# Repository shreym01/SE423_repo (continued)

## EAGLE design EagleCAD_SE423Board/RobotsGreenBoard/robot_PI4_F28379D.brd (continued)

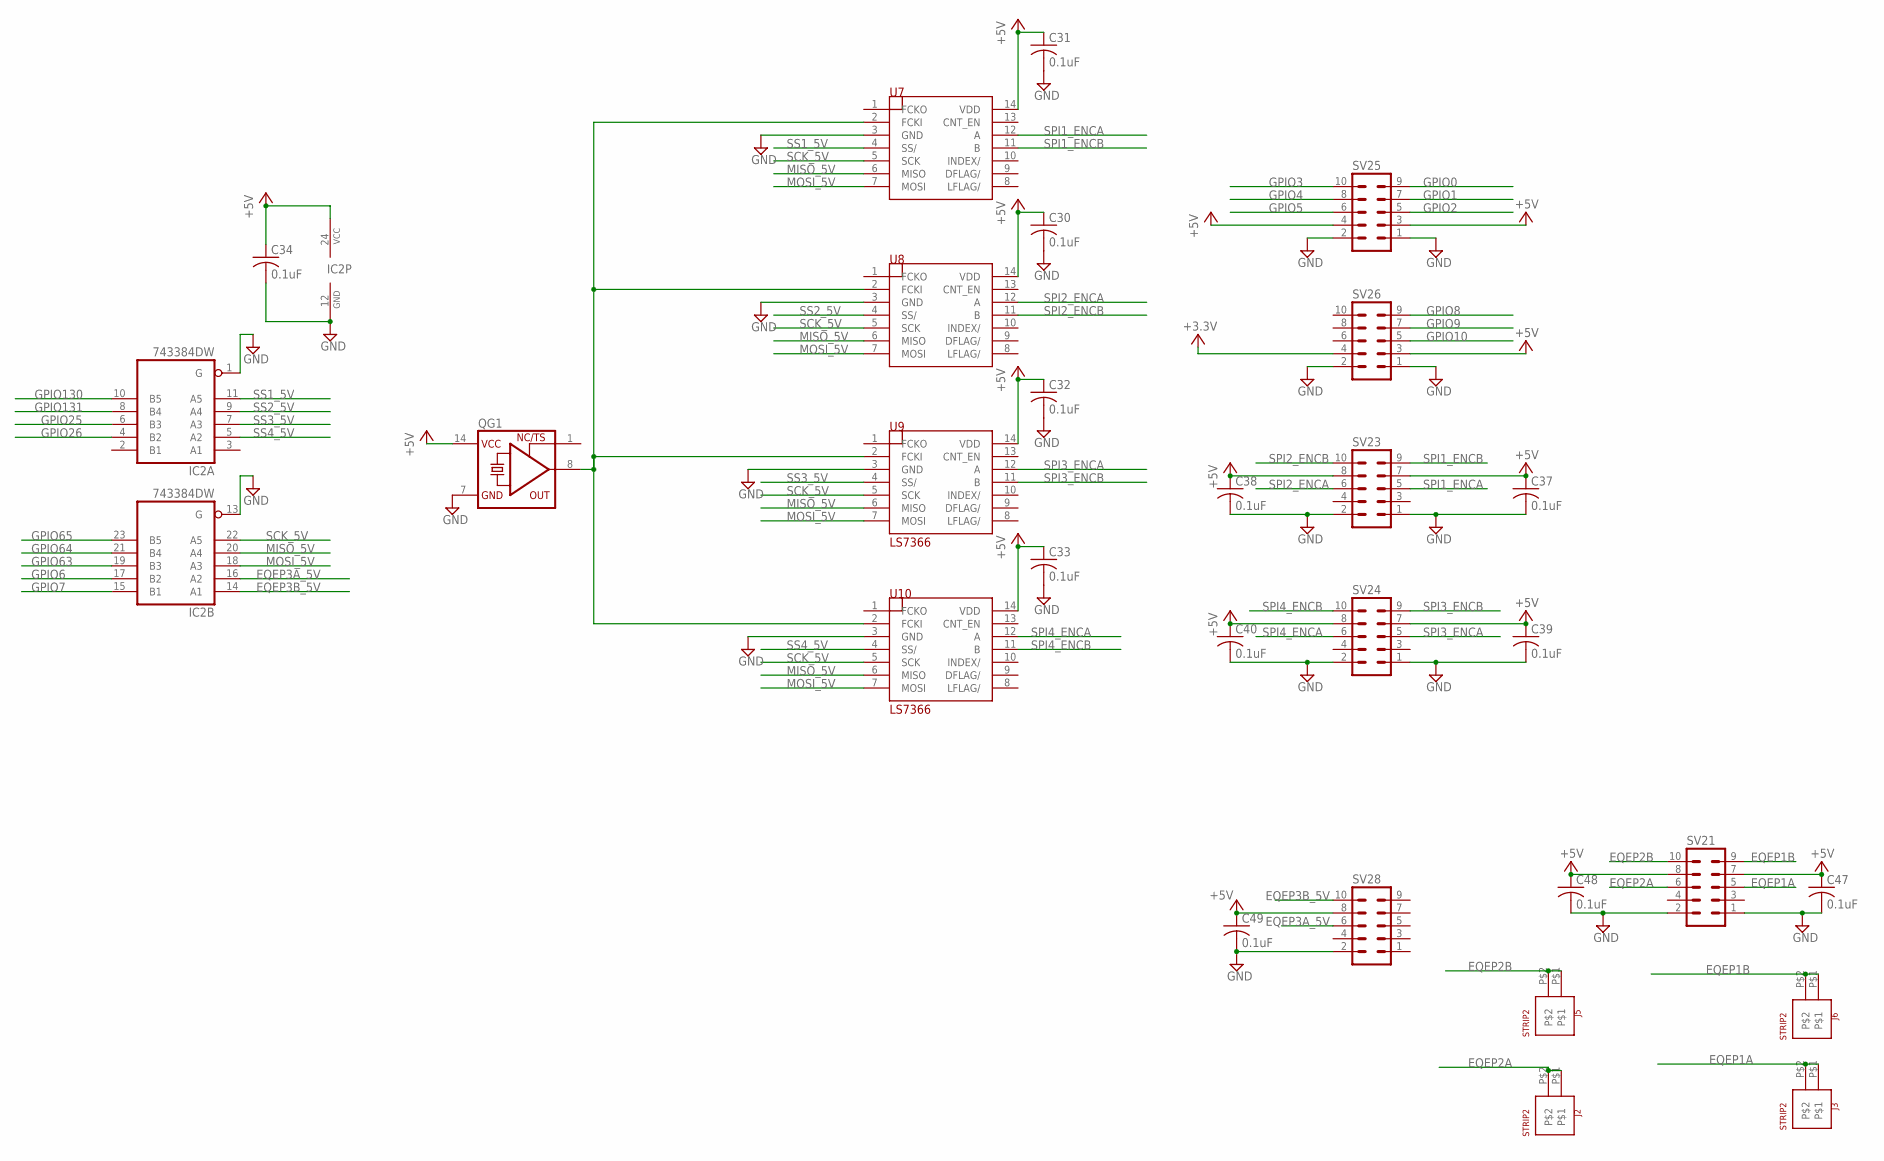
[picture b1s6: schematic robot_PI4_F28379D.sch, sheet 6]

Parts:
C30, C31, C32, C33, C34, C37, C38, C39, C40, C47, C48, C49: 0.1uF; C1206
IC2: 743384DW; SO24W
J2, J3, J5, J6: STRIP2
QG1: XO-14; DIL14S
SV21, SV23, SV24, SV25, SV26, SV28: MA05-2
U7, U8: LS7366R; SO14
U9, U10: LS7366; SO14

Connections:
+3.3V: SV26.4; also elsewhere on the board
+5V: C30.1, C31.1, C32.1, C33.1, C34.1, C37.1, C38.1, C39.1, C40.1, C47.1, C48.1, C49.1, IC2.24 (VCC), QG1.14 (VCC), SV21.7, SV21.8, SV23.7, SV23.8, SV24.7, SV24.8, SV25.3, SV25.4, SV26.3, SV28.8, U7.14 (VDD), U8.14 (VDD), U9.14 (VDD), U10.14 (VDD); also elsewhere on the board
EQEP1A: J3.P$1, J3.P$2, SV21.5
EQEP1B: J6.P$1, J6.P$2, SV21.9
EQEP2A: J2.P$1, J2.P$2, SV21.6
EQEP2B: J5.P$1, J5.P$2, SV21.10
EQEP3A_5V: IC2.16 (A2), SV28.6
EQEP3B_5V: IC2.14 (A1), SV28.10
GND: C30.2, C31.2, C32.2, C33.2, C34.2, C37.2, C38.2, C39.2, C40.2, C47.2, C48.2, C49.2, IC2.1 (G), IC2.12 (GND), IC2.13 (G), QG1.7 (GND), SV21.1, SV21.2, SV23.1, SV23.2, SV24.1, SV24.2, SV25.1, SV25.2, SV26.1, SV26.2, SV28.2, U7.3 (GND), U8.3 (GND), U9.3 (GND), U10.3 (GND); also elsewhere on the board
GPIO0: SV25.9; also elsewhere on the board
GPIO1: SV25.7; also elsewhere on the board
GPIO2: SV25.5; also elsewhere on the board
GPIO3: SV25.10; also elsewhere on the board
GPIO4: SV25.8; also elsewhere on the board
GPIO5: SV25.6; also elsewhere on the board
GPIO6: IC2.17 (B2); also elsewhere on the board
GPIO7: IC2.15 (B1); also elsewhere on the board
GPIO8: SV26.9; also elsewhere on the board
GPIO9: SV26.7; also elsewhere on the board
GPIO10: SV26.5; also elsewhere on the board
GPIO25: IC2.6 (B3); also elsewhere on the board
GPIO26: IC2.4 (B2); also elsewhere on the board
GPIO63: IC2.19 (B3); also elsewhere on the board
GPIO64: IC2.21 (B4); also elsewhere on the board
GPIO65: IC2.23 (B5); also elsewhere on the board
GPIO130: IC2.10 (B5); also elsewhere on the board
GPIO131: IC2.8 (B4); also elsewhere on the board
MISO_5V: IC2.20 (A4), U7.6 (MISO), U8.6 (MISO), U9.6 (MISO), U10.6 (MISO)
MOSI_5V: IC2.18 (A3), U7.7 (MOSI), U8.7 (MOSI), U9.7 (MOSI), U10.7 (MOSI)
unnamed: QG1.8 (OUT), U7.2 (FCKI), U8.2 (FCKI), U9.2 (FCKI), U10.2 (FCKI)
SCK_5V: IC2.22 (A5), U7.5 (SCK), U8.5 (SCK), U9.5 (SCK), U10.5 (SCK)
SPI1_ENCA: SV23.5, U7.12 (A)
SPI1_ENCB: SV23.9, U7.11 (B)
SPI2_ENCA: SV23.6, U8.12 (A)
SPI2_ENCB: SV23.10, U8.11 (B)
SPI3_ENCA: SV24.5, U9.12 (A)
SPI3_ENCB: SV24.9, U9.11 (B)
SPI4_ENCA: SV24.6, U10.12 (A)
SPI4_ENCB: SV24.10, U10.11 (B)
SS1_5V: IC2.11 (A5), U7.4 (SS/)
SS2_5V: IC2.9 (A4), U8.4 (SS/)
SS3_5V: IC2.7 (A3), U9.4 (SS/)
SS4_5V: IC2.5 (A2), U10.4 (SS/)

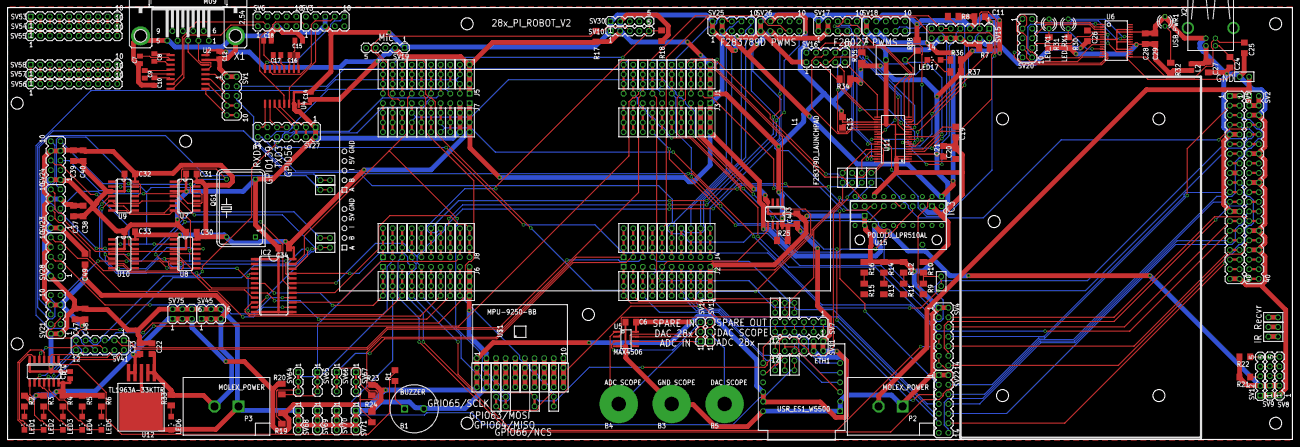
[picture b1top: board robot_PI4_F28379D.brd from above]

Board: 2 copper layers, 339.1 x 114.0 mm, 270 parts (0 on the bottom side), 281 nets.

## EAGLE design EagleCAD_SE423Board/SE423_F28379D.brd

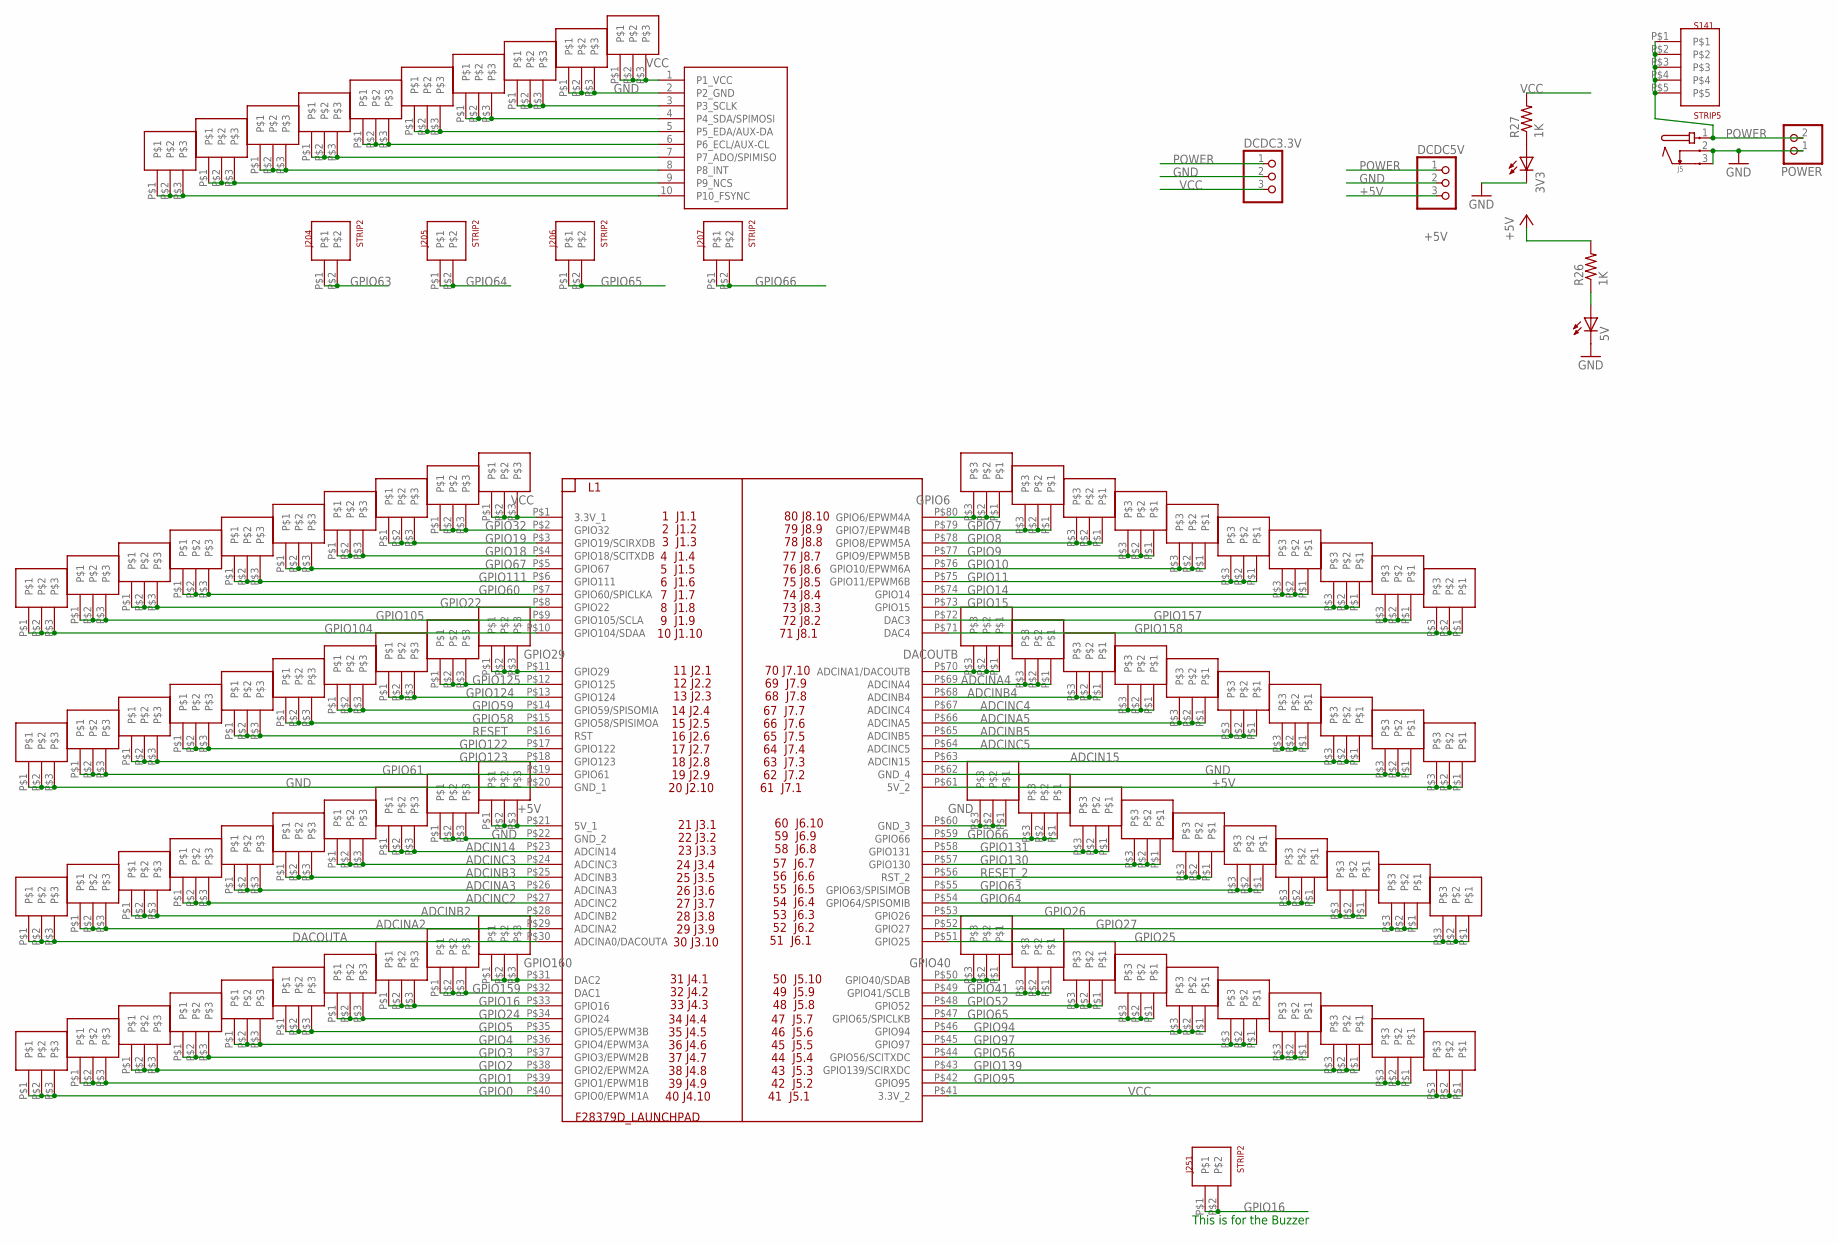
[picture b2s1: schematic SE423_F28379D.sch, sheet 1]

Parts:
3V3, 5V: LEDCHIPLED_1206; CHIPLED_1206
DCDC3.3V, DCDC5V: PINHD-1X3; 1X03
J5: JACK-PMS
J10, J14, J15, J16, J17, J18, J19, J20, J21, J28, J29, J30, J31, J32, J33, J98, J99, J100, J101, J102, J103, J104, J105, J106, J107, J108, J109, J110, J111, J112, J113, J114, J115, J116, J117, J118, J119, J120, J121, J122, J123, J124, J125, J126, J127, J128, J129, J130, J131, J132, J133, J134, J135, J136, J137, J138, J139, J140, J141, J142, J143, J144, J145, J146, J147, J148, J149, J150, J151, J152, J153, J154, J155, J156, J157, J158, J159, J160, J161, J162, J163, J164, J165, J166, J167, J168, J169, J170, J176, J177: STRIP3
J204, J205, J206, J207, J251: STRIP2
L1: F28379D_LAUNCHPAD
POWER: PINHD-1X2; 1X02
R26, R27: 1K; M1206
S141: STRIP5
U$1: MPU-9250-BB

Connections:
+5V: DCDC5V.3, J103.P$1, J103.P$2, J103.P$3, J152.P$1, J152.P$2, J152.P$3, L1.P$21 (5V_1), L1.P$61 (5V_2), R26.2; also elsewhere on the board
ADCIN14: J105.P$1, J105.P$2, J105.P$3, L1.P$23 (ADCIN14)
ADCIN15: J150.P$1, J150.P$2, J150.P$3, L1.P$63 (ADCIN15)
ADCINA2: J111.P$1, J111.P$2, J111.P$3, L1.P$29 (ADCINA2); also elsewhere on the board
ADCINA3: J108.P$1, J108.P$2, J108.P$3, L1.P$26 (ADCINA3); also elsewhere on the board
ADCINA4: J144.P$1, J144.P$2, J144.P$3, L1.P$69 (ADCINA4)
ADCINA5: J147.P$1, J147.P$2, J147.P$3, L1.P$66 (ADCINA5)
ADCINB2: J110.P$1, J110.P$2, J110.P$3, L1.P$28 (ADCINB2)
ADCINB3: J107.P$1, J107.P$2, J107.P$3, L1.P$25 (ADCINB3)
ADCINB4: J145.P$1, J145.P$2, J145.P$3, L1.P$68 (ADCINB4); also elsewhere on the board
ADCINB5: J148.P$1, J148.P$2, J148.P$3, L1.P$65 (ADCINB5)
ADCINC2: J109.P$1, J109.P$2, J109.P$3, L1.P$27 (ADCINC2)
ADCINC3: J106.P$1, J106.P$2, J106.P$3, L1.P$24 (ADCINC3)
ADCINC4: J146.P$1, J146.P$2, J146.P$3, L1.P$67 (ADCINC4)
ADCINC5: J149.P$1, J149.P$2, J149.P$3, L1.P$64 (ADCINC5)
DACOUTA: J112.P$1, J112.P$2, J112.P$3, L1.P$30 (ADCINA0/DACOUTA)
DACOUTB: J143.P$1, J143.P$2, J143.P$3, L1.P$70 (ADCINA1/DACOUTB)
GND: 3V3.C, 5V.C, DCDC3.3V.2, DCDC5V.2, J5.2, J5.3, J102.P$1, J102.P$2, J102.P$3, J104.P$1, J104.P$2, J104.P$3, J124.P$1, J124.P$2, J124.P$3, J151.P$1, J151.P$2, J151.P$3, J153.P$1, J153.P$2, J153.P$3, L1.P$20 (GND_1), L1.P$22 (GND_2), L1.P$60 (GND_3), L1.P$62 (GND_4), POWER.1, U$1.2 (P2_GND); also elsewhere on the board
GPIO0: J122.P$1, J122.P$2, J122.P$3, L1.P$40 (GPIO0/EPWM1A); also elsewhere on the board
GPIO1: J121.P$1, J121.P$2, J121.P$3, L1.P$39 (GPIO1/EPWM1B); also elsewhere on the board
GPIO2: J120.P$1, J120.P$2, J120.P$3, L1.P$38 (GPIO2/EPWM2A); also elsewhere on the board
GPIO3: J119.P$1, J119.P$2, J119.P$3, L1.P$37 (GPIO3/EPWM2B); also elsewhere on the board
GPIO4: J118.P$1, J118.P$2, J118.P$3, L1.P$36 (GPIO4/EPWM3A); also elsewhere on the board
GPIO5: J117.P$1, J117.P$2, J117.P$3, L1.P$35 (GPIO5/EPWM3B); also elsewhere on the board
GPIO6: J133.P$1, J133.P$2, J133.P$3, L1.P$80 (GPIO6/EPWM4A); also elsewhere on the board
GPIO7: J134.P$1, J134.P$2, J134.P$3, L1.P$79 (GPIO7/EPWM4B); also elsewhere on the board
GPIO8: J135.P$1, J135.P$2, J135.P$3, L1.P$78 (GPIO8/EPWM5A); also elsewhere on the board
GPIO9: J136.P$1, J136.P$2, J136.P$3, L1.P$77 (GPIO9/EPWM5B); also elsewhere on the board
GPIO10: J137.P$1, J137.P$2, J137.P$3, L1.P$76 (GPIO10/EPWM6A); also elsewhere on the board
GPIO11: J138.P$1, J138.P$2, J138.P$3, L1.P$75 (GPIO11/EPWM6B); also elsewhere on the board
GPIO14: J139.P$1, J139.P$2, J139.P$3, L1.P$74 (GPIO14); also elsewhere on the board
GPIO15: J140.P$1, J140.P$2, J140.P$3, L1.P$73 (GPIO15); also elsewhere on the board
GPIO16: J115.P$1, J115.P$2, J115.P$3, J251.P$1, J251.P$2, L1.P$33 (GPIO16)
GPIO18: J16.P$1, J16.P$2, J16.P$3, L1.P$4 (GPIO18/SCITXDB); also elsewhere on the board
GPIO19: J15.P$1, J15.P$2, J15.P$3, L1.P$3 (GPIO19/SCIRXDB); also elsewhere on the board
GPIO22: J20.P$1, J20.P$2, J20.P$3, L1.P$8 (GPIO22); also elsewhere on the board
GPIO24: J116.P$1, J116.P$2, J116.P$3, L1.P$34 (GPIO24); also elsewhere on the board
GPIO25: J162.P$1, J162.P$2, J162.P$3, L1.P$51 (GPIO25); also elsewhere on the board
GPIO26: J160.P$1, J160.P$2, J160.P$3, L1.P$53 (GPIO26); also elsewhere on the board
GPIO27: J161.P$1, J161.P$2, J161.P$3, L1.P$52 (GPIO27); also elsewhere on the board
GPIO29: J29.P$1, J29.P$2, J29.P$3, L1.P$11 (GPIO29); also elsewhere on the board
GPIO32: J14.P$1, J14.P$2, J14.P$3, L1.P$2 (GPIO32); also elsewhere on the board
GPIO40: J163.P$1, J163.P$2, J163.P$3, L1.P$50 (GPIO40/SDAB); also elsewhere on the board
GPIO41: J164.P$1, J164.P$2, J164.P$3, L1.P$49 (GPIO41/SCLB); also elsewhere on the board
GPIO52: J165.P$1, J165.P$2, J165.P$3, L1.P$48 (GPIO52)
GPIO56: J169.P$1, J169.P$2, J169.P$3, L1.P$44 (GPIO56/SCITXDC); also elsewhere on the board
GPIO58: J33.P$1, J33.P$2, J33.P$3, L1.P$15 (GPIO58/SPISIMOA); also elsewhere on the board
GPIO59: J32.P$1, J32.P$2, J32.P$3, L1.P$14 (GPIO59/SPISOMIA); also elsewhere on the board
GPIO60: J19.P$1, J19.P$2, J19.P$3, L1.P$7 (GPIO60/SPICLKA); also elsewhere on the board
GPIO61: J101.P$1, J101.P$2, J101.P$3, L1.P$19 (GPIO61); also elsewhere on the board
GPIO63: J158.P$1, J158.P$2, J158.P$3, J204.P$1, J204.P$2, L1.P$55 (GPIO63/SPISIMOB); also elsewhere on the board
GPIO64: J159.P$1, J159.P$2, J159.P$3, J205.P$1, J205.P$2, L1.P$54 (GPIO64/SPISOMIB); also elsewhere on the board
GPIO65: J166.P$1, J166.P$2, J166.P$3, J206.P$1, J206.P$2, L1.P$47 (GPIO65/SPICLKB); also elsewhere on the board
GPIO66: J154.P$1, J154.P$2, J154.P$3, J207.P$1, J207.P$2, L1.P$59 (GPIO66)
GPIO67: J17.P$1, J17.P$2, J17.P$3, L1.P$5 (GPIO67)
GPIO94: J167.P$1, J167.P$2, J167.P$3, L1.P$46 (GPIO94); also elsewhere on the board
GPIO95: J176.P$1, J176.P$2, J176.P$3, L1.P$42 (GPIO95); also elsewhere on the board
GPIO97: J168.P$1, J168.P$2, J168.P$3, L1.P$45 (GPIO97); also elsewhere on the board
GPIO104: J28.P$1, J28.P$2, J28.P$3, L1.P$10 (GPIO104/SDAA)
GPIO105: J21.P$1, J21.P$2, J21.P$3, L1.P$9 (GPIO105/SCLA)
GPIO111: J18.P$1, J18.P$2, J18.P$3, L1.P$6 (GPIO111); also elsewhere on the board
GPIO122: J99.P$1, J99.P$2, J99.P$3, L1.P$17 (GPIO122); also elsewhere on the board
GPIO123: J100.P$1, J100.P$2, J100.P$3, L1.P$18 (GPIO123); also elsewhere on the board
GPIO124: J31.P$1, J31.P$2, J31.P$3, L1.P$13 (GPIO124); also elsewhere on the board
GPIO125: J30.P$1, J30.P$2, J30.P$3, L1.P$12 (GPIO125); also elsewhere on the board
GPIO130: J156.P$1, J156.P$2, J156.P$3, L1.P$57 (GPIO130); also elsewhere on the board
GPIO131: J155.P$1, J155.P$2, J155.P$3, L1.P$58 (GPIO131); also elsewhere on the board
GPIO139: J170.P$1, J170.P$2, J170.P$3, L1.P$43 (GPIO139/SCIRXDC); also elsewhere on the board
GPIO157: J141.P$1, J141.P$2, J141.P$3, L1.P$72 (DAC3); also elsewhere on the board
GPIO158: J142.P$1, J142.P$2, J142.P$3, L1.P$71 (DAC4); also elsewhere on the board
GPIO159: J114.P$1, J114.P$2, J114.P$3, L1.P$32 (DAC1); also elsewhere on the board
GPIO160: J113.P$1, J113.P$2, J113.P$3, L1.P$31 (DAC2); also elsewhere on the board
unnamed: 3V3.A, R27.1
unnamed: 5V.A, R26.1
unnamed: J125.P$1, J125.P$2, J125.P$3, U$1.3 (P3_SCLK)
unnamed: J126.P$1, J126.P$2, J126.P$3, U$1.4 (P4_SDA/SPIMOSI)
unnamed: J127.P$1, J127.P$2, J127.P$3, U$1.5 (P5_EDA/AUX-DA)
unnamed: J128.P$1, J128.P$2, J128.P$3, U$1.6 (P6_ECL/AUX-CL)
unnamed: J129.P$1, J129.P$2, J129.P$3, U$1.7 (P7_ADO/SPIMISO)
unnamed: J130.P$1, J130.P$2, J130.P$3, U$1.8 (P8_INT)
unnamed: J131.P$1, J131.P$2, J131.P$3, U$1.9 (P9_NCS)
unnamed: J132.P$1, J132.P$2, J132.P$3, U$1.10 (P10_FSYNC)
POWER: DCDC3.3V.1, DCDC5V.1, J5.1, POWER.2, S141.P$1, S141.P$2, S141.P$3, S141.P$4, S141.P$5; also elsewhere on the board
RESET: J98.P$1, J98.P$2, J98.P$3, L1.P$16 (RST)
RESET_2: J157.P$1, J157.P$2, J157.P$3, L1.P$56 (RST_2)
VCC: DCDC3.3V.3, J10.P$1, J10.P$2, J10.P$3, J123.P$1, J123.P$2, J123.P$3, J177.P$1, J177.P$2, J177.P$3, L1.P$1 (3.3V_1), L1.P$41 (3.3V_2), R27.2, U$1.1 (P1_VCC); also elsewhere on the board

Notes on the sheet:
This is for the Buzzer

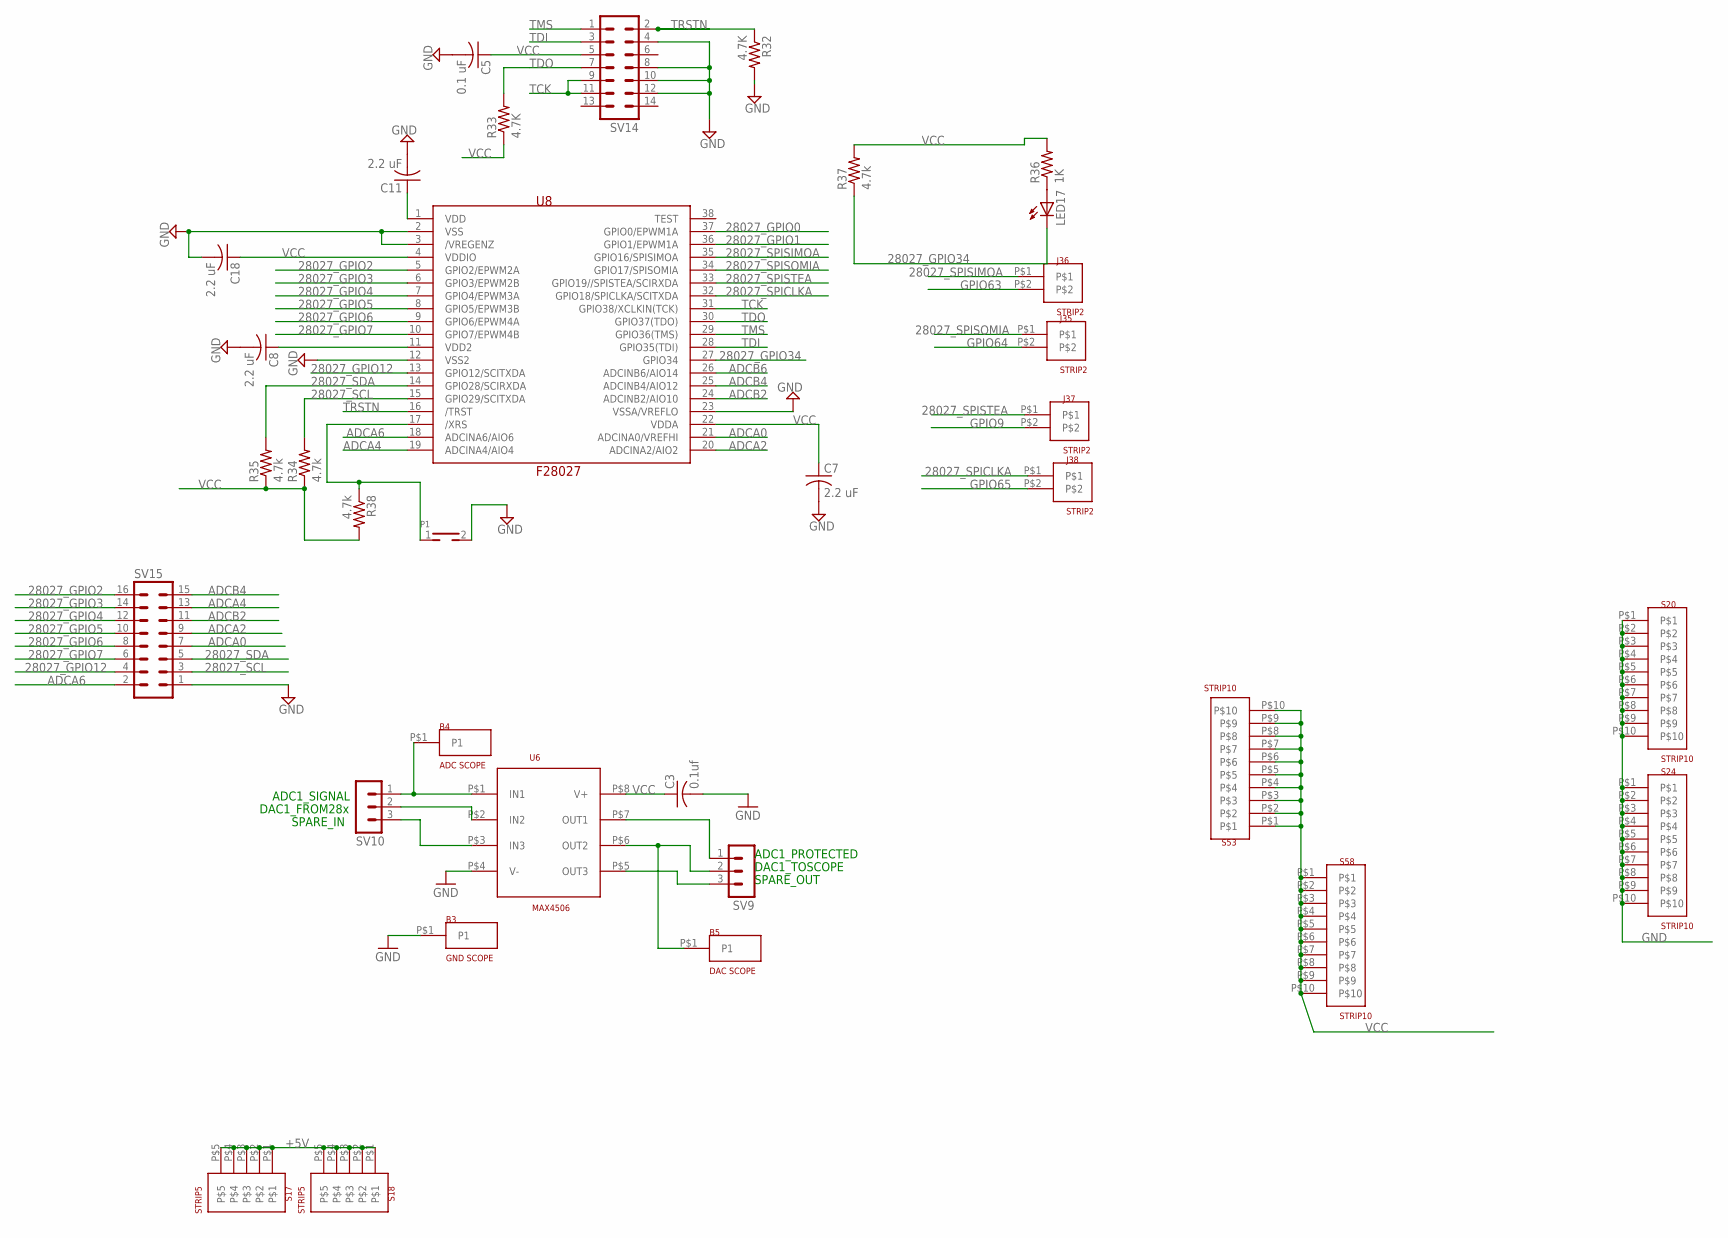
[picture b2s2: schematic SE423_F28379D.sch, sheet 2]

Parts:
B3: GND SCOPE; BANANA_MALE
B4: ADC SCOPE; BANANA_MALE
B5: DAC SCOPE; BANANA_MALE
C3: 0.1uf; C1206
C5: 0.1 uF; C1206
C7, C8, C11, C18: 2.2 uF; C1206
J35, J36, J37, J38: STRIP2
LED17: LEDCHIPLED_1206; CHIPLED_1206
P1: TH_PUSHBOTTON; TH_PUSHBUTTON
R32, R33: 4.7K; M1206
R34, R35, R37, R38: 4.7k; M1206
R36: 1K; M1206
S17, S18: STRIP5
S20, S24, S53, S58: STRIP10
SV9, SV10: MA03-1
SV14: MA07-2
SV15: MA08-2
U6: MAX4506; SOIC-8
U8: F28027; DA38

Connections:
28027_GPIO0: U8.37 (GPIO0/EPWM1A); also elsewhere on the board
28027_GPIO1: U8.36 (GPIO1/EPWM1A); also elsewhere on the board
28027_GPIO2: SV15.16, U8.5 (GPIO2/EPWM2A)
28027_GPIO3: SV15.14, U8.6 (GPIO3/EPWM2B)
28027_GPIO4: SV15.12, U8.7 (GPIO4/EPWM3A)
28027_GPIO5: SV15.10, U8.8 (GPIO5/EPWM3B)
28027_GPIO6: SV15.8, U8.9 (GPIO6/EPWM4A)
28027_GPIO7: SV15.6, U8.10 (GPIO7/EPWM4B)
28027_GPIO12: SV15.4, U8.13 (GPIO12/SCITXDA)
28027_GPIO34: LED17.C, R37.1, U8.27 (GPIO34)
28027_SCL: R34.2, SV15.3, U8.15 (GPIO29/SCITXDA)
28027_SDA: R35.2, SV15.5, U8.14 (GPIO28/SCIRXDA)
28027_SPICLKA: J38.P$1, U8.32 (GPIO18/SPICLKA/SCITXDA)
28027_SPISIMOA: J36.P$1, U8.35 (GPIO16/SPISIMOA)
28027_SPISOMIA: J35.P$1, U8.34 (GPIO17/SPISOMIA)
28027_SPISTEA: J37.P$1, U8.33 (GPIO19//SPISTEA/SCIRXDA)
+5V: S17.P$1, S17.P$2, S17.P$3, S17.P$4, S17.P$5, S18.P$1, S18.P$2, S18.P$3, S18.P$4, S18.P$5; also elsewhere on the board
ADCA0: SV15.7, U8.21 (ADCINA0/VREFHI)
ADCA2: SV15.9, U8.20 (ADCINA2/AIO2)
ADCA4: SV15.13, U8.19 (ADCINA4/AIO4)
ADCA6: SV15.2, U8.18 (ADCINA6/AIO6)
ADCB2: SV15.11, U8.24 (ADCINB2/AIO10)
ADCB4: SV15.15, U8.25 (ADCINB4/AIO12)
ADCB6: U8.26 (ADCINB6/AIO14)
GND: B3.P$1, C3.2, C5.2, C7.2, C8.2, C11.2, C18.2, P1.2, R32.2, S20.P$1, S20.P$2, S20.P$3, S20.P$4, S20.P$5, S20.P$6, S20.P$7, S20.P$8, S20.P$9, S20.P$10, S24.P$1, S24.P$2, S24.P$3, S24.P$4, S24.P$5, S24.P$6, S24.P$7, S24.P$8, S24.P$9, S24.P$10, SV14.4, SV14.8, SV14.10, SV14.12, SV15.1, U6.P$4 (V-), U8.2 (VSS), U8.3 (/VREGENZ), U8.12 (VSS2), U8.23 (VSSA/VREFLO); also elsewhere on the board
GPIO9: J37.P$2; also elsewhere on the board
GPIO63: J36.P$2; also elsewhere on the board
GPIO64: J35.P$2; also elsewhere on the board
GPIO65: J38.P$2; also elsewhere on the board
unnamed: SV9.1, U6.P$7 (OUT1)
unnamed: B5.P$1, SV9.2, U6.P$6 (OUT2)
unnamed: SV9.3, U6.P$5 (OUT3)
unnamed: B4.P$1, SV10.1, U6.P$1 (IN1)
unnamed: SV10.2, U6.P$2 (IN2)
unnamed: SV10.3, U6.P$3 (IN3)
unnamed: C11.1, U8.1 (VDD)
unnamed: C8.1, U8.11 (VDD2)
unnamed: P1.1, R38.1, U8.17 (/XRS)
unnamed: LED17.A, R36.1
TCK: SV14.9, SV14.11, U8.31 (GPIO38/XCLKIN(TCK))
TDI: SV14.3, U8.28 (GPIO35(TDI))
TDO: R33.2, SV14.7, U8.30 (GPIO37(TDO))
TMS: SV14.1, U8.29 (GPIO36(TMS))
TRSTN: R32.1, SV14.2, U8.16 (/TRST)
VCC: C3.1, C5.1, C7.1, C18.1, R33.1, R34.1, R35.1, R36.2, R37.2, R38.2, S53.P$1, S53.P$2, S53.P$3, S53.P$4, S53.P$5, S53.P$6, S53.P$7, S53.P$8, S53.P$9, S53.P$10, S58.P$1, S58.P$2, S58.P$3, S58.P$4, S58.P$5, S58.P$6, S58.P$7, S58.P$8, S58.P$9, S58.P$10, SV14.5, U6.P$8 (V+), U8.4 (VDDIO), U8.22 (VDDA); also elsewhere on the board

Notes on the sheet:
ADC1_SIGNAL
ADC1_PROTECTED
DAC1_FROM28x
DAC1_TOSCOPE
SPARE_IN
SPARE_OUT

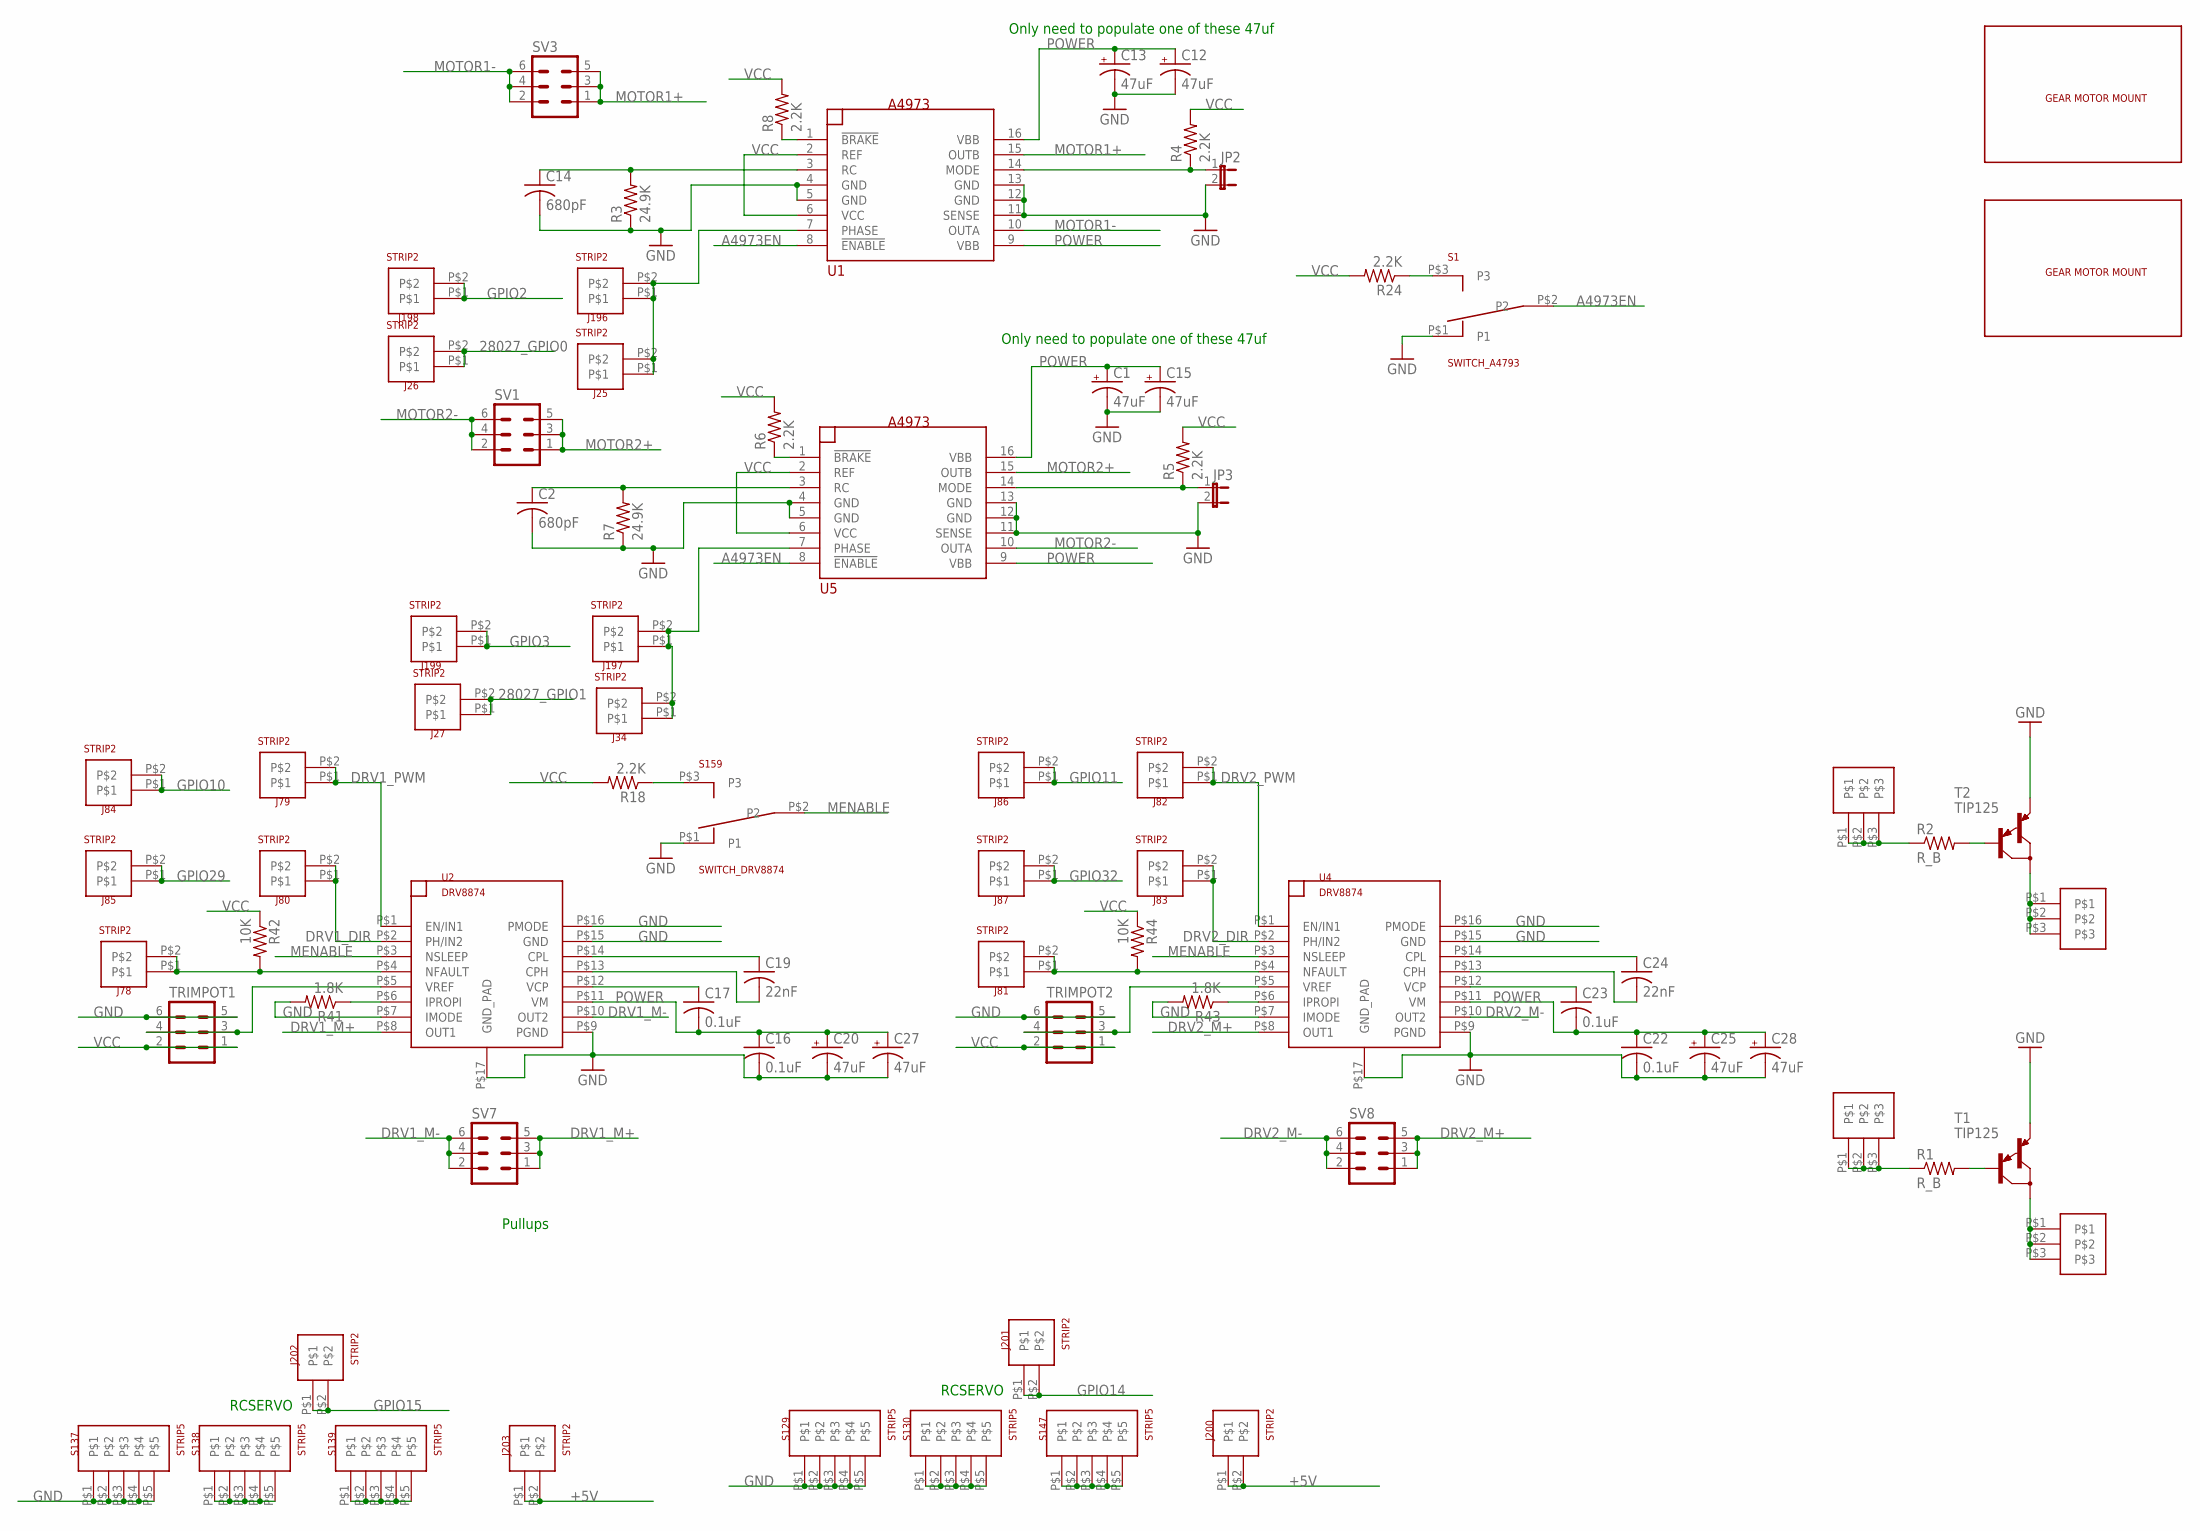
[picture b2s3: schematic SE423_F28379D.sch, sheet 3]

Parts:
C1, C12, C13, C15, C20, C25, C27, C28: 47uF; 153CLV-0810
C2, C14: 680pF; C1206
C16, C17, C22, C23: 0.1uF; C1206
C19, C24: 22nF; C1206
J4, J6, J23, J24: STRIP3
J25, J26, J27, J34, J78, J79, J80, J81, J82, J83, J84, J85, J86, J87, J196, J197, J198, J199, J200, J201, J202, J203: STRIP2
JP2, JP3: JP1E; JP1
R1, R2: R_B; 0207/10
R3, R7: 24.9K; M1206
R4, R5, R6, R8, R18, R24: 2.2K; M1206
R41, R43: 1.8K; M1206
R42, R44: 10K; M1206
S1: SWITCH_A4793; SWITCH_SLIDE
S129, S130, S137, S138, S139, S147: STRIP5
S159: SWITCH_DRV8874; SWITCH_SLIDE
SV1, SV3, SV7, SV8: MA03-2
T1, T2: TIP125; TO220
TRIMPOT1, TRIMPOT2: MA03-2
U1, U5: A4973; SO16W_LONGERPINS
U2, U4: DRV8874; HTSSOP16
U$2, U$3: GEARMOTOR_MOUNT

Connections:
28027_GPIO0: J26.P$1, J26.P$2; also elsewhere on the board
28027_GPIO1: J27.P$1, J27.P$2; also elsewhere on the board
+5V: J200.P$1, J200.P$2, J203.P$1, J203.P$2; also elsewhere on the board
A4973EN: S1.P$2 (P2), U1.8 (!ENABLE), U5.8 (!ENABLE)
DRV1_DIR: J80.P$1, J80.P$2, U2.P$2 (PH/IN2)
DRV1_M+: SV7.1, SV7.3, SV7.5, U2.P$8 (OUT1)
DRV1_M-: SV7.2, SV7.4, SV7.6, U2.P$10 (OUT2)
DRV1_PWM: J79.P$1, J79.P$2, U2.P$1 (EN/IN1)
DRV2_DIR: J83.P$1, J83.P$2, U4.P$2 (PH/IN2)
DRV2_M+: SV8.1, SV8.3, SV8.5, U4.P$8 (OUT1)
DRV2_M-: SV8.2, SV8.4, SV8.6, U4.P$10 (OUT2)
DRV2_PWM: J82.P$1, J82.P$2, U4.P$1 (EN/IN1)
GND: C1.-, C2.2, C12.-, C13.-, C14.2, C15.-, C16.2, C20.-, C22.2, C25.-, C27.-, C28.-, JP2.2, JP3.2, R3.1, R7.1, R41.2, R43.2, S1.P$1 (P1), S129.P$1, S129.P$2, S129.P$3, S129.P$4, S129.P$5, S137.P$1, S137.P$2, S137.P$3, S137.P$4, S137.P$5, S159.P$1 (P1), T1.3 (E), T2.3 (E), TRIMPOT1.5, TRIMPOT1.6, TRIMPOT2.5, TRIMPOT2.6, U1.4 (GND), U1.5 (GND), U1.11 (SENSE), U1.12 (GND), U1.13 (GND), U2.P$7 (IMODE), U2.P$9 (PGND), U2.P$15 (GND), U2.P$16 (PMODE), U2.P$17 (GND_PAD), U4.P$7 (IMODE), U4.P$9 (PGND), U4.P$15 (GND), U4.P$16 (PMODE), U4.P$17 (GND_PAD), U5.4 (GND), U5.5 (GND), U5.11 (SENSE), U5.12 (GND), U5.13 (GND); also elsewhere on the board
GPIO2: J198.P$1, J198.P$2; also elsewhere on the board
GPIO3: J199.P$1, J199.P$2; also elsewhere on the board
GPIO10: J84.P$1, J84.P$2; also elsewhere on the board
GPIO11: J86.P$1, J86.P$2; also elsewhere on the board
GPIO14: J201.P$1, J201.P$2; also elsewhere on the board
GPIO15: J202.P$1, J202.P$2; also elsewhere on the board
GPIO29: J85.P$1, J85.P$2; also elsewhere on the board
GPIO32: J87.P$1, J87.P$2; also elsewhere on the board
MENABLE: S159.P$2 (P2), U2.P$3 (NSLEEP), U4.P$3 (NSLEEP)
MOTOR1+: SV3.1, SV3.3, SV3.5, U1.15 (OUTB)
MOTOR1-: SV3.2, SV3.4, SV3.6, U1.10 (OUTA)
MOTOR2+: SV1.1, SV1.3, SV1.5, U5.15 (OUTB)
MOTOR2-: SV1.2, SV1.4, SV1.6, U5.10 (OUTA)
unnamed: R24.1, S1.P$3 (P3)
unnamed: S139.P$1, S139.P$2, S139.P$3, S139.P$4, S139.P$5
unnamed: S147.P$1, S147.P$2, S147.P$3, S147.P$4, S147.P$5
unnamed: R2.2, T2.1 (B)
unnamed: R1.2, T1.1 (B)
unnamed: S138.P$1, S138.P$2, S138.P$3, S138.P$4, S138.P$5
unnamed: R6.1, U5.1 (!BRAKE)
unnamed: C2.1, R7.2, U5.3 (RC)
unnamed: R8.1, U1.1 (!BRAKE)
unnamed: C14.1, R3.2, U1.3 (RC)
unnamed: JP2.1, R4.1, U1.14 (MODE)
unnamed: R18.1, S159.P$3 (P3)
unnamed: JP3.1, R5.1, U5.14 (MODE)
unnamed: C19.1, U2.P$14 (CPL)
unnamed: C19.2, U2.P$13 (CPH)
unnamed: C17.1, U2.P$12 (VCP)
unnamed: R43.1, U4.P$6 (IPROPI)
unnamed: R41.1, U2.P$6 (IPROPI)
unnamed: J78.P$1, J78.P$2, R42.2, U2.P$4 (NFAULT)
unnamed: TRIMPOT1.3, TRIMPOT1.4, U2.P$5 (VREF)
unnamed: C24.1, U4.P$14 (CPL)
unnamed: C24.2, U4.P$13 (CPH)
unnamed: C23.1, U4.P$12 (VCP)
unnamed: J81.P$1, J81.P$2, R44.2, U4.P$4 (NFAULT)
unnamed: TRIMPOT2.3, TRIMPOT2.4, U4.P$5 (VREF)
unnamed: S130.P$1, S130.P$2, S130.P$3, S130.P$4, S130.P$5
unnamed: J25.P$1, J25.P$2, J196.P$1, J196.P$2, U1.7 (PHASE)
unnamed: J34.P$1, J34.P$2, J197.P$1, J197.P$2, U5.7 (PHASE)
POWER: C1.+, C12.+, C13.+, C15.+, C16.1, C17.2, C20.+, C22.1, C23.2, C25.+, C27.+, C28.+, U1.9 (VBB), U1.16 (VBB), U2.P$11 (VM), U4.P$11 (VM), U5.9 (VBB), U5.16 (VBB); also elsewhere on the board
TR_BASE: J6.P$1, J6.P$2, J6.P$3, R1.1
TR_BASE1: J24.P$1, J24.P$2, J24.P$3, R2.1
TR_LOAD: J4.P$1, J4.P$2, J4.P$3, T1.2 (C)
TR_LOAD1: J23.P$1, J23.P$2, J23.P$3, T2.2 (C)
VCC: R4.2, R5.2, R6.2, R8.2, R18.2, R24.2, R42.1, R44.1, TRIMPOT1.1, TRIMPOT1.2, TRIMPOT2.1, TRIMPOT2.2, U1.2 (REF), U1.6 (VCC), U5.2 (REF), U5.6 (VCC); also elsewhere on the board

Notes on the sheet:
Pullups
RCSERVO
Only need to populate one of these 47uf
